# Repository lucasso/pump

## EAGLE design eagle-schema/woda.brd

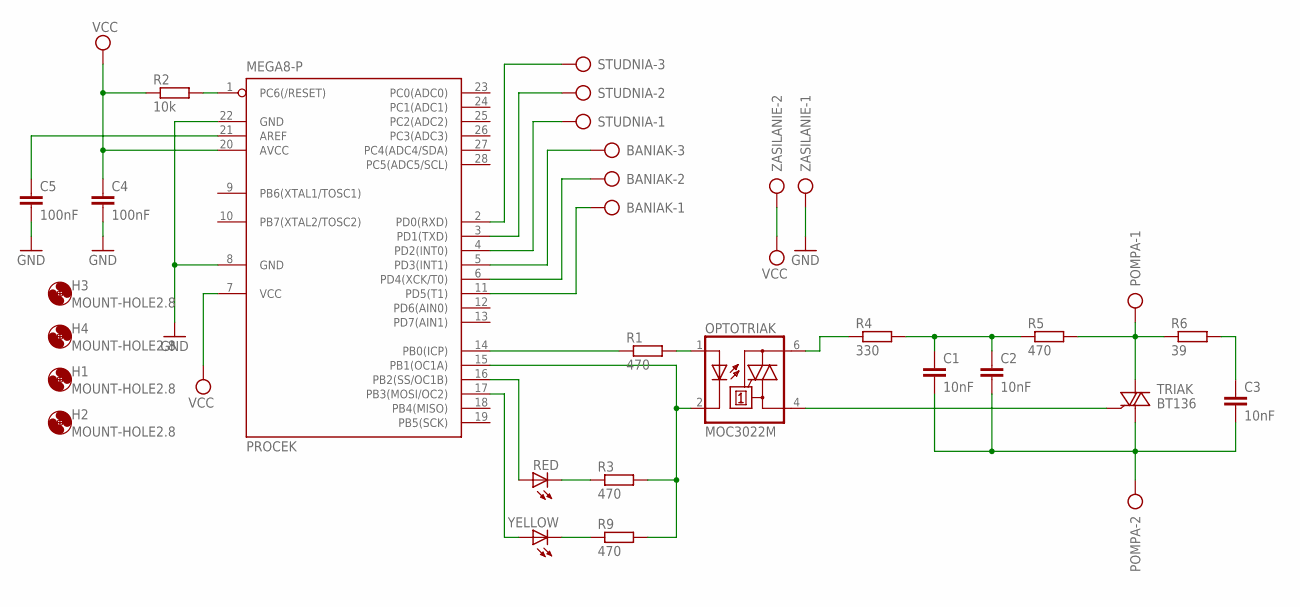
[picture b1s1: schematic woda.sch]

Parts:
BANIAK: AK300/3
C1, C2, C3: 10nF; C10B4
C4, C5: 100nF; C2.5-2
H1, H2, H3, H4: MOUNT-HOLE2.8; 2,8
OPTOTRIAK: MOC3022M; DIL06
POMPA: AK300/2
PROCEK: MEGA8-P; DIL28-3
R1, R3, R9: 470; 0207/15
R2: 10k; 0207/15
R4: 330; 0207/7
R5: 470; 0207/7
R6: 39; 0207/7
RED: LED3MM
STUDNIA: AK300/3
TRIAK: BT136; TO220AB
YELLOW: LED3MM
ZASILANIE: AK300/2

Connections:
GND: C4.2, C5.2, PROCEK.8 (GND), PROCEK.22 (GND), ZASILANIE.1
unnamed: OPTOTRIAK.2 (C), PROCEK.15 (PB1(OC1A)), R3.2, R9.2
unnamed: C1.2, C2.2, C3.2, POMPA.2, TRIAK.1 (A1)
unnamed: OPTOTRIAK.1 (A), R1.2
unnamed: C5.1, PROCEK.21 (AREF)
unnamed: PROCEK.1 (PC6(/RESET)), R2.2
unnamed: PROCEK.2 (PD0(RXD)), STUDNIA.3
unnamed: PROCEK.3 (PD1(TXD)), STUDNIA.2
unnamed: PROCEK.4 (PD2(INT0)), STUDNIA.1
unnamed: BANIAK.3, PROCEK.5 (PD3(INT1))
unnamed: BANIAK.2, PROCEK.6 (PD4(XCK/T0))
unnamed: BANIAK.1, PROCEK.11 (PD5(T1))
unnamed: PROCEK.16 (PB2(SS/OC1B)), RED.A
unnamed: PROCEK.17 (PB3(MOSI/OC2)), YELLOW.A
unnamed: R3.1, RED.K (C)
unnamed: R9.1, YELLOW.K (C)
unnamed: PROCEK.14 (PB0(ICP)), R1.1
unnamed: POMPA.1, R5.2, R6.1, TRIAK.2 (A2)
unnamed: OPTOTRIAK.4 (A1), TRIAK.3 (G)
unnamed: C3.1, R6.2
unnamed: OPTOTRIAK.6 (A2), R4.1
unnamed: C1.1, C2.1, R4.2, R5.1
VCC: C4.1, PROCEK.7 (VCC), PROCEK.20 (AVCC), R2.1, ZASILANIE.2

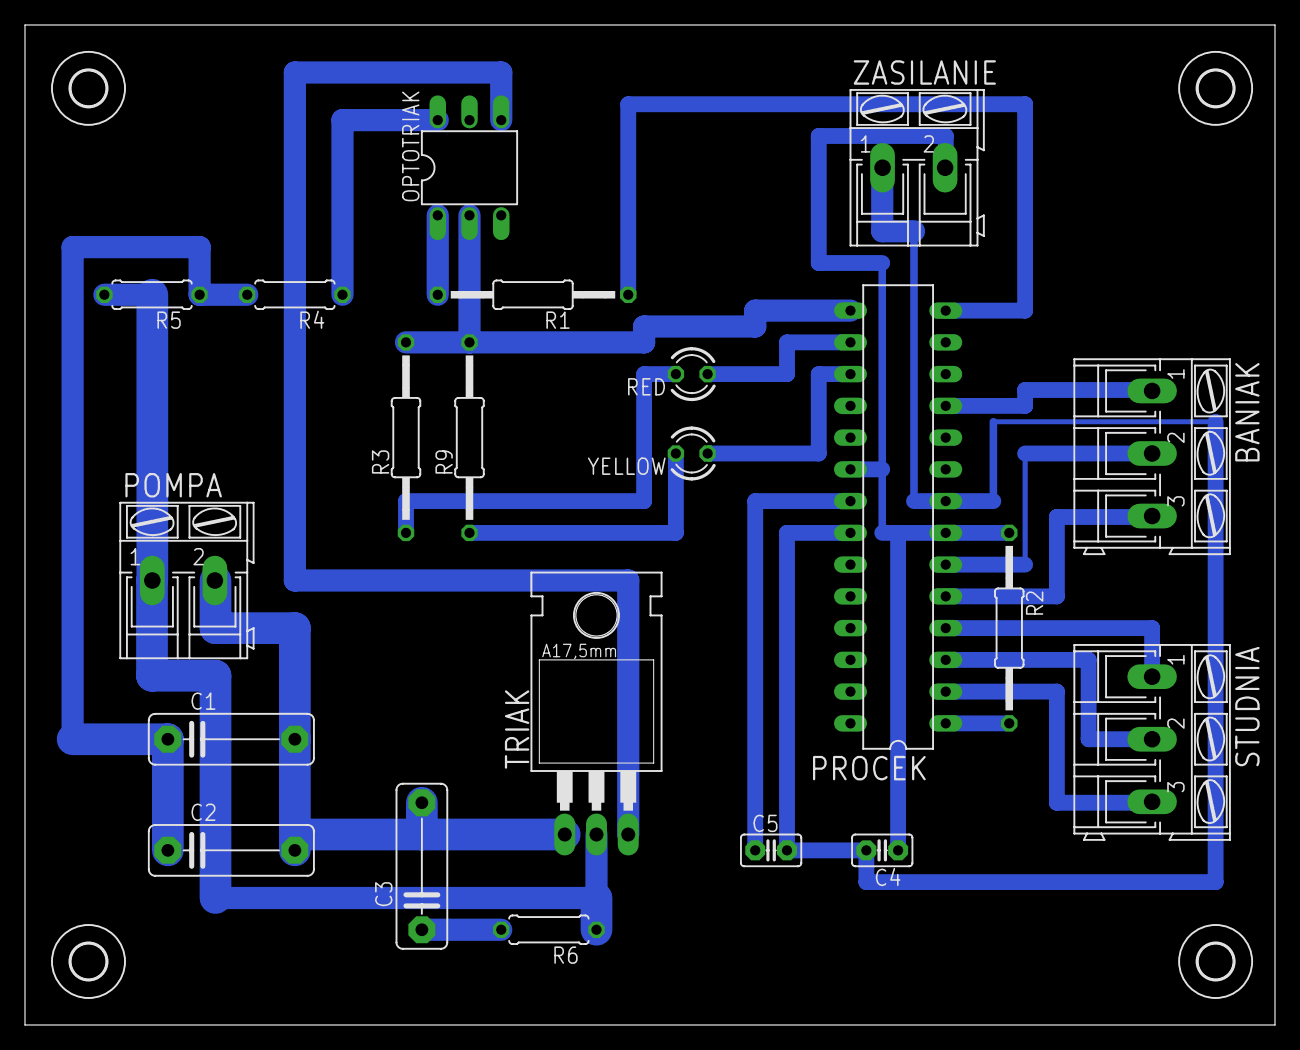
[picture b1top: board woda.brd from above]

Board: 2 copper layers, 100.0 x 80.0 mm, 25 parts (0 on the bottom side), 23 nets.

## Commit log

2014-05-22 woda, powinno dzialac
2019-10-28 added some scripts
2019-10-28 added eagle schema files
